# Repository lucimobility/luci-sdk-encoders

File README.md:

# luci-sdk-encoders #
Please note all documentation lives in the [docs folder](docs/1_encoders.md) or at the 
[LUCI SDK](https://lucimobility.github.io/luci-ros2-sdk-docs/) website.

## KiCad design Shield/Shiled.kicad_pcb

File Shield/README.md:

# Shield #

All docs for the shield live [here](../docs/2_shield.md)

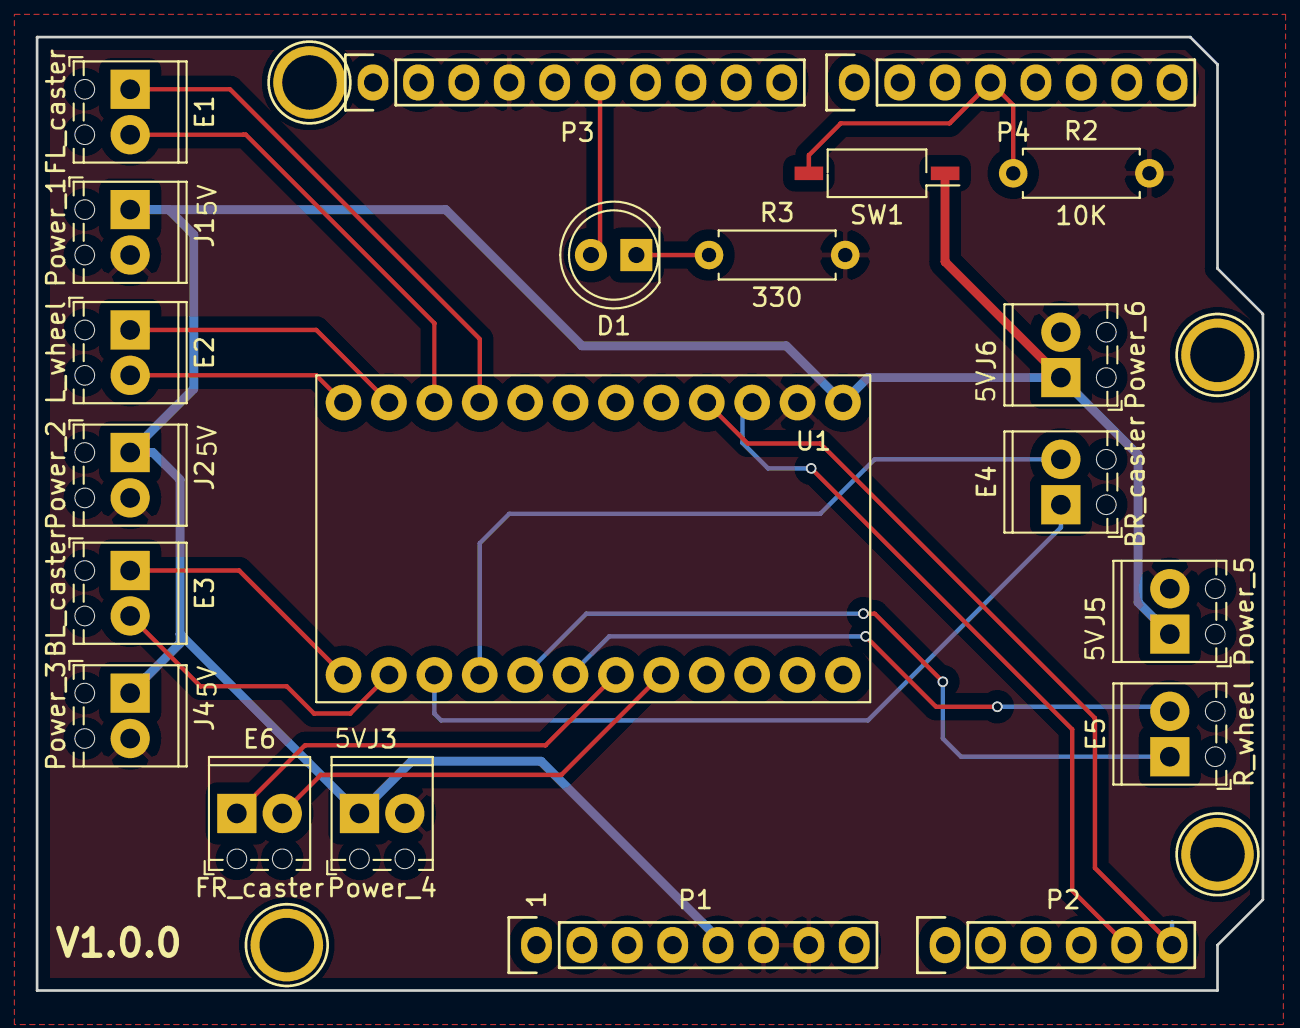
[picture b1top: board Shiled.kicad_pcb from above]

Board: 2 copper layers, 68.6 x 53.3 mm, 25 parts (0 on the bottom side), 19 nets.

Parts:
D1: LED; LED_D5.0mm
E1: FL_caster; TerminalBlock_Phoenix_MPT-0,5-2-2.54_1x02_P2.54mm_Horizontal
E2: L_wheel; TerminalBlock_Phoenix_MPT-0,5-2-2.54_1x02_P2.54mm_Horizontal
E3: BL_caster; TerminalBlock_Phoenix_MPT-0,5-2-2.54_1x02_P2.54mm_Horizontal
E4: BR_caster; TerminalBlock_Phoenix_MPT-0,5-2-2.54_1x02_P2.54mm_Horizontal
E5: R_wheel; TerminalBlock_Phoenix_MPT-0,5-2-2.54_1x02_P2.54mm_Horizontal
E6: FR_caster; TerminalBlock_Phoenix_MPT-0,5-2-2.54_1x02_P2.54mm_Horizontal
J1: Power_1; TerminalBlock_Phoenix_MPT-0,5-2-2.54_1x02_P2.54mm_Horizontal
J2: Power_2; TerminalBlock_Phoenix_MPT-0,5-2-2.54_1x02_P2.54mm_Horizontal
J3: Power_4; TerminalBlock_Phoenix_MPT-0,5-2-2.54_1x02_P2.54mm_Horizontal
J4: Power_3; TerminalBlock_Phoenix_MPT-0,5-2-2.54_1x02_P2.54mm_Horizontal
J5: Power_5; TerminalBlock_Phoenix_MPT-0,5-2-2.54_1x02_P2.54mm_Horizontal
J6: Power_6; TerminalBlock_Phoenix_MPT-0,5-2-2.54_1x02_P2.54mm_Horizontal
P1: Power; Socket_Strip_Arduino_1x08
P2: Analog; Socket_Strip_Arduino_1x06
P3: Digital; Socket_Strip_Arduino_1x10
P4: Digital; Socket_Strip_Arduino_1x08
P5, P6, P7, P8: CONN_01X01; Arduino_1pin
R2: 10K; R_Axial_DIN0207_L6.3mm_D2.5mm_P7.62mm_Horizontal
R3: 330; R_Axial_DIN0207_L6.3mm_D2.5mm_P7.62mm_Horizontal
SW1: SW_DIP_x01; SW_DIP_SPSTx01_Slide_Copal_CHS-01B_W7.62mm_P1.27mm
U1: TCA9548A

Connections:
4: P4.4, R2.1, SW1.2
12(MISO): D1.2, P3.6
+5V: J1.1, J2.1, J3.1, J4.1, J5.1, J6.1, P1.5, SW1.1, U1.1
A4(SDA): P2.5, P3.2, U1.3
A5(SCL): P2.6, P3.1, U1.4
GND: J1.2, J2.2, J3.2, J4.2, J5.2, J6.2, P1.6, P1.7, P3.4, R2.2, R3.2, U1.2
unnamed: D1.1, R3.1
SC0: E1.2, U1.10
SC1: E2.2, U1.12
SC2: E3.2, U1.14
SC3: E4.2, U1.16
SC4: E5.2, U1.18
SC5: E6.2, U1.20
SD0: E1.1, U1.9
SD1: E2.1, U1.11
SD2: E3.1, U1.13
SD3: E4.1, U1.15
SD4: E5.1, U1.17
SD5: E6.1, U1.19

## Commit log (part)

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2023-05-31 Inital Commit
2023-06-06 Added encoder.md file
2023-06-06 Added shield, firmware, encoder docs
2023-06-06 squash
2023-06-07 Added hardware files
2023-06-07 Added links
2023-06-15 Updated docs
2023-06-16 Added assembly image
2023-07-27 added STL files for Q500M printed parts
2023-12-12 change some function calls due to library change
2024-02-01 Edited code to work with just drive wheels and changed magnet detection logic
2024-02-06 swapped library along with api changes
2024-02-06 add karls multiplier
2024-02-13 Increase update rate
2024-03-06 Added millisecond timestamp
2024-03-06 Update docs for direct mount design
2024-06-13 update due to library changes
2024-10-15 remove extra index in data buffer
2025-07-16 copying over the PR temp from SDK for consistent information
2025-07-16 Add error buffer and error handling. Only send encoder angle data if both left and right have valid data
